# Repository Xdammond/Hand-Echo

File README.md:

# Hand Echo

## Overview
Hand Echo is a wireless robotic hand teleoperation system designed to replicate user hand movements through a sensor-equipped glove and servo-actuated robotic hand.

## Project Goals
- Capture finger motion using wearable sensors
- Transmit motion data wirelessly between microcontrollers
- Control a robotic hand in real time
- Build a modular system with separate glove, receiver, and mechanical subsystems
- Document hardware, firmware, testing, and lessons learned

## Subsystems

### Glove Controller
The glove controller measures finger movement using sensors mounted to a wearable glove. Sensor data is read by a microcontroller, processed, and prepared for wireless transmission.

### Wireless Communication
The wireless link sends motion data from the glove controller to the robotic hand receiver. This subsystem includes packet formatting, transmission timing, and reliability testing.

### Robotic Hand Receiver
The robotic hand receiver interprets incoming wireless data and controls servos to reproduce finger motion on the robotic hand.

## Repository Structure
docs/          System documentation and engineering notes
hardware/      Schematics, wiring diagrams, and BOMs
firmware/      Microcontroller code
media/         Images, videos, and diagrams
test_data/     Test results and measurements

## Status
Completed

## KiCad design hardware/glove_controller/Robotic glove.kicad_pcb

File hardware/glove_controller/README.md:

# Glove Controller

Contains:

- Sensor information
- Wiring diagrams
- Schematics
- Calibration data

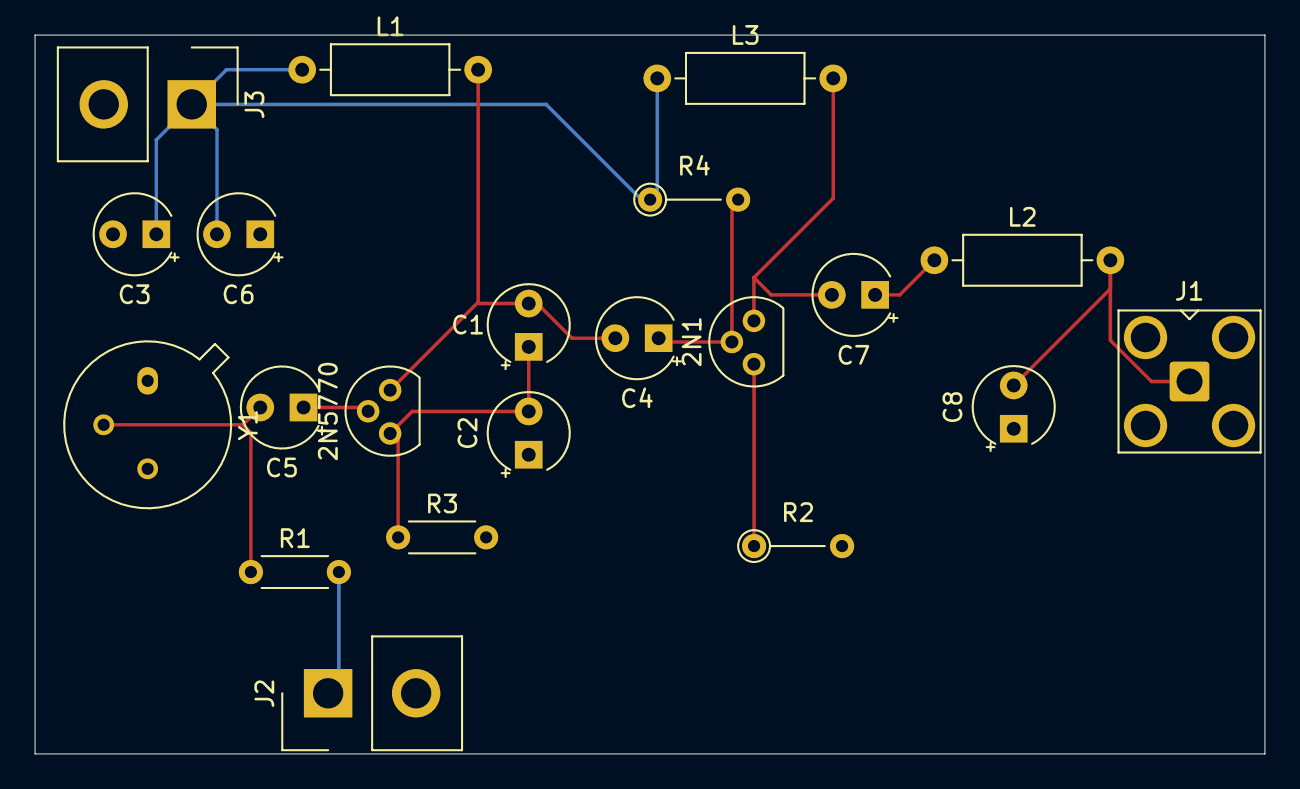
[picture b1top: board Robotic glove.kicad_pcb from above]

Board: 4 copper layers, 71.0 x 41.5 mm, 21 parts (0 on the bottom side), 12 nets.

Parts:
2N1, 2N5770: Q_NPN_CBE; TO-92L
C1: 7.5pF; CP_Radial_Tantal_D4.5mm_P2.50mm
C2: 15pF; CP_Radial_Tantal_D4.5mm_P2.50mm
C3, C6: 100nF; CP_Radial_Tantal_D4.5mm_P2.50mm
C4: 10pF; CP_Radial_Tantal_D4.5mm_P2.50mm
C5, C7: 100pF; CP_Radial_Tantal_D4.5mm_P2.50mm
C8: 22pF; CP_Radial_Tantal_D4.5mm_P2.50mm
J1: 132134-15; SMA_Amphenol_901-143_Horizontal
J2, J3: Conn_01x02; Samtec_HPM-02-05-x-S_Straight_1x02_Pitch5.08mm
L1, L3: 27nH; L_Axial_L6.6mm_D2.7mm_P10.16mm_Horizontal_Vishay_IM-2
L2: 23nH; L_Axial_L6.6mm_D2.7mm_P10.16mm_Horizontal_Vishay_IM-2
R1: 33k; R_Axial_DIN0204_L3.6mm_D1.6mm_P5.08mm_Horizontal
R2, R4: 100; R_Axial_DIN0204_L3.6mm_D1.6mm_P5.08mm_Vertical
R3: 68; R_Axial_DIN0204_L3.6mm_D1.6mm_P5.08mm_Horizontal
Y1: Crystal_GND3; TO-39-3

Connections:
+5V: C3.1, C6.2, J3.1, L1.1, L3.1, R4.1
/Arduino TX in: J2.1, R1.2
Earth: C2.1, C3.2, C6.1, C8.1, J1.2, J2.2, J3.2, R2.2, R3.2, Y1.1, Y1.3
unnamed: 2N1.2 (B), C4.1, R4.2
unnamed: 2N1.1 (C), C7.2, L3.2
unnamed: 2N1.3 (E), R2.1
unnamed: 2N5770.2 (B), C5.1
unnamed: 2N5770.1 (C), C1.2, C4.2, L1.2
unnamed: 2N5770.3 (E), C1.1, C2.2, R3.1
unnamed: C5.2, R1.1, Y1.2
unnamed: C7.1, L2.1
unnamed: C8.2, J1.1, L2.2

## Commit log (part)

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2026-05-29 Revise README with project overview and goals
    Updated project description and added detailed sections on goals, subsystems, and repository structure.
2026-05-29 Update system overview with new content
2026-05-29 Add system overview section to documentation
2026-05-29 Add README for robotic hand project
2026-06-10 Create photos
